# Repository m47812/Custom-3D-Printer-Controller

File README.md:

# Custom-3D-Printer-Controller
A fully custom 3D Printer controller board based on a stm32f7 controller with TMC2209 stepper drivers

## Summary

This Repo contains the design files for a fully custom 3D printer controller board. It is equipped with an STM32F7 Controller and uses custom-made 
TMC2209 Driver PCBs (also included in the Repo). The PCB was designed for using JLCPCBs Assembly service, so most of the SMD parts can directly be assembled by them. 
The Controller PCB is a two layer board, which makes production for hobby projects more affordable.

## Repo Content
The Project contains 3 Folders with KiCad design files.
- Main board: The main board PCB containing the STM32

- Motor Driver: The TMC2209 Motor Driver Plug-In Board

- Handheld: A Handheld device that can be connected via SPI to manually drive the stepper motors.

## Key Points
- STM32F7 Controller
- TMC2209 Stepper Driver
- 24V Power Supply
- USB-B Micro
- Micro SD-Card Slot
- Z Stepper Drivers Allow for simple parallel and serial motor connection
- 3 End stops
- 4 Fan Ports
  - 1 Individually PWM controllable
  - 2 PWM Controllable together
  - 1 Always On
- Support of two Extruders
- SWD Programming Interface
- SPI Connector
- UART Connector
- Buffer Battery
- WLAN Module

## Background
I designed this 3D printer controller as a hobby project, for my own 3D printer. The original plan was to build a custom hardware and custom firmware. Throughout 
the project my colleague and I have moved to a different printer design which resulted in the stop of the firmware project. The PCB was produced at JLCPCB and I did
some tests with it. I've decided to make the project open source for anyone who would like to build their own 3D printer electronics. The project may serve as a starting point or something to enhance, modify and customize.

## State of the project

Since the project was not continued on the firmware side, I did not have the possibility of testing all features to a full degree. My tests manly focused on using the
the motor drivers together with the STM32. I haven't found any problems so far with the PCB, but I would advise looking over it yourself before you order it. 

### Functions I used
- Use of Motor Drivers with STM32 Controller (Configuration via UART & and Control via Step Dir interface)
- Communication via USB
- Power supply from 24V and USB (controller only without motors for USB power)
- Programming with ST-Link

### Untested Functions
- Temperature Measurements
- Temperature control of Bed and Extruders
- SD Card Slot
- WLAN Module
- Buffer Battery

## Firmware
I would recommend using the board with [Marlin firmware](https://github.com/MarlinFirmware/Marlin). It will require some manual adaptations to be able to use Marlin.
Since I haven't used Marlin in my own project, I can not provide these adaptations here.

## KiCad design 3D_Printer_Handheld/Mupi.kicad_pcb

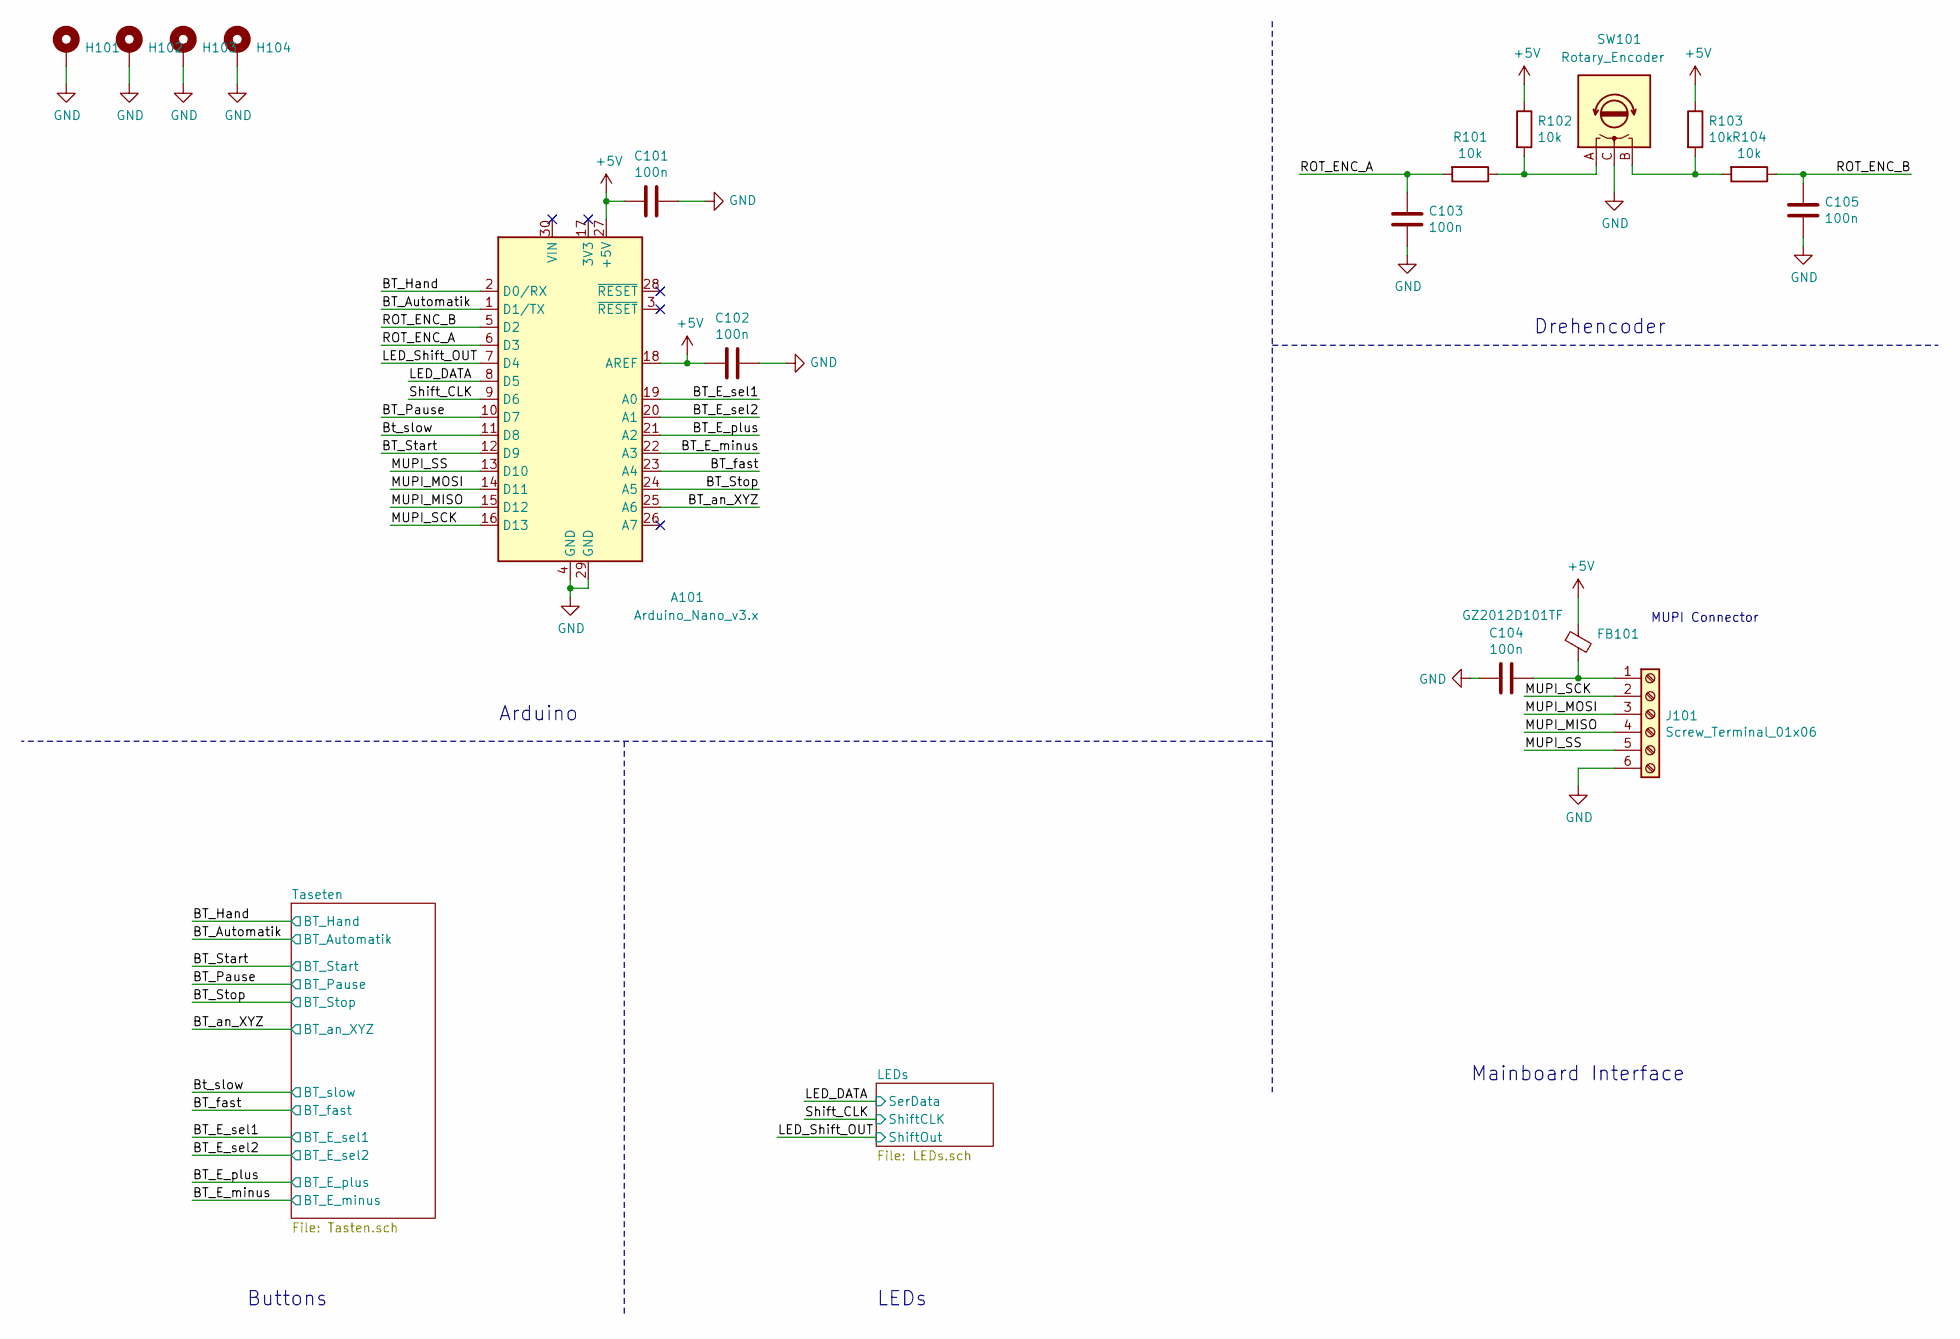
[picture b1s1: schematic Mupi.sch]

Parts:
A101: Arduino_Nano_v3.x; Arduino_Nano
C101, C102, C103, C104, C105: 100n; C_0805_2012Metric_Pad1.15x1.40mm_HandSolder
FB101: GZ2012D101TF; R_0805_2012Metric
H101, H102, H103, H104: MountingHole_Pad; MountingHole_3.2mm_M3_Pad_Via
J101: Screw_Terminal_01x06; TerminalBlock_Phoenix_MPT-0,5-6-2.54_1x06_P2.54mm_Horizontal
R101, R102, R103, R104: 10k; R_0805_2012Metric_Pad1.15x1.40mm_HandSolder
SW101: Rotary_Encoder; RotaryEncoder_Alps_EC12E_Vertical_H20mm

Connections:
+5V: A101.18 (AREF), A101.27 (+5V), C101.2, C102.2, FB101.1, R102.1, R103.1; also elsewhere on the board
/BT_Automatik: A101.1 (D1/TX); also elsewhere on the board
/BT_E_minus: A101.22 (A3); also elsewhere on the board
/BT_E_plus: A101.21 (A2); also elsewhere on the board
/BT_E_sel1: A101.19 (A0); also elsewhere on the board
/BT_E_sel2: A101.20 (A1); also elsewhere on the board
/BT_Hand: A101.2 (D0/RX); also elsewhere on the board
/BT_Pause: A101.10 (D7); also elsewhere on the board
/BT_Start: A101.12 (D9); also elsewhere on the board
/BT_Stop: A101.24 (A5); also elsewhere on the board
/BT_an_XYZ: A101.25 (A6); also elsewhere on the board
/BT_fast: A101.23 (A4); also elsewhere on the board
/Bt_slow: A101.11 (D8); also elsewhere on the board
/LED_DATA: A101.8 (D5); also elsewhere on the board
/LED_Shift_OUT: A101.7 (D4); also elsewhere on the board
/MUPI_MISO: A101.15 (D12), J101.4
/MUPI_MOSI: A101.14 (D11), J101.3
/MUPI_SCK: A101.16 (D13), J101.2
/MUPI_SS: A101.13 (D10), J101.5
/Shift_CLK: A101.9 (D6); also elsewhere on the board
GND: A101.4 (GND), A101.29 (GND), C101.1, C102.1, C103.2, C104.2, C105.2, H101.1, H102.1, H103.1, H104.1, J101.6, SW101.C; also elsewhere on the board
unnamed: C104.1, FB101.2, J101.1
unnamed: R101.1, R102.2, SW101.A
unnamed: R103.2, R104.2, SW101.B

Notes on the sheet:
Drehencoder
MUPI Connector
Mainboard Interface
Buttons
LEDs
Arduino

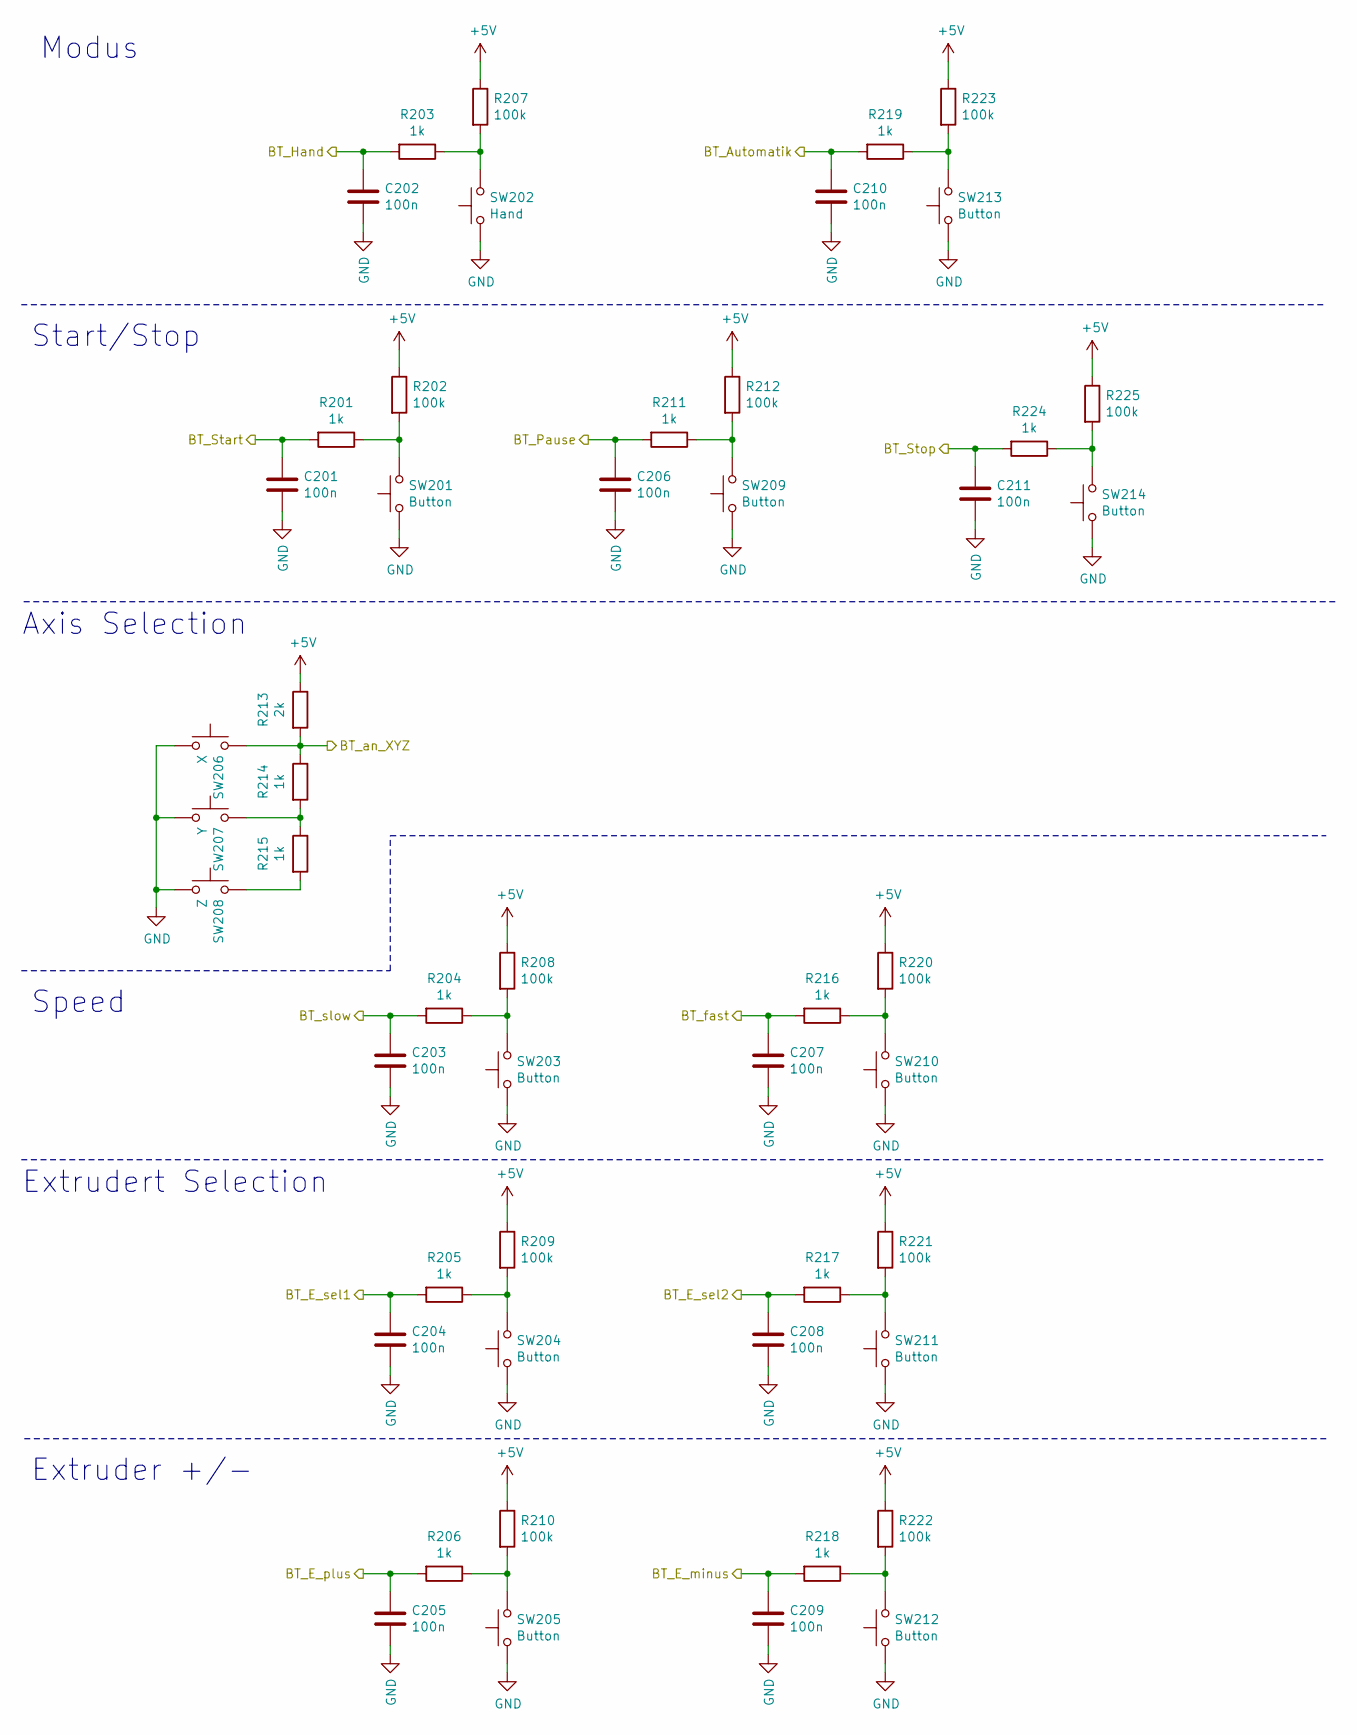
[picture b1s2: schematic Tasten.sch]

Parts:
C201, C202, C203, C204, C205, C206, C207, C208, C209, C210, C211: 100n; C_0805_2012Metric_Pad1.15x1.40mm_HandSolder
R201, R203, R204, R205, R206, R211, R214, R215, R216, R217, R218, R219, R224: 1k; R_0805_2012Metric_Pad1.15x1.40mm_HandSolder
R202, R207, R208, R209, R210, R212, R220, R221, R222, R223, R225: 100k; R_0805_2012Metric_Pad1.15x1.40mm_HandSolder
R213: 2k; R_0805_2012Metric_Pad1.15x1.40mm_HandSolder
SW201, SW203, SW204, SW205, SW209, SW210, SW211, SW212, SW213, SW214: Button; SW_SPST_TL3342
SW202: Hand; SW_SPST_TL3342
SW206: X; SW_SPST_TL3342
SW207: Y; SW_SPST_TL3342
SW208: Z; SW_SPST_TL3342

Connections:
+5V: R202.1, R207.1, R208.1, R209.1, R210.1, R212.1, R213.1, R220.1, R221.1, R222.1, R223.1, R225.1; also elsewhere on the board
/BT_Automatik: C210.2, R219.2; also elsewhere on the board
/BT_E_minus: C209.2, R218.2; also elsewhere on the board
/BT_E_plus: C205.2, R206.2; also elsewhere on the board
/BT_E_sel1: C204.2, R205.2; also elsewhere on the board
/BT_E_sel2: C208.2, R217.2; also elsewhere on the board
/BT_Hand: C202.2, R203.2; also elsewhere on the board
/BT_Pause: C206.2, R211.2; also elsewhere on the board
/BT_Start: C201.2, R201.2; also elsewhere on the board
/BT_Stop: C211.2, R224.2; also elsewhere on the board
/BT_an_XYZ: R213.2, R214.1, SW206.2; also elsewhere on the board
/BT_fast: C207.2, R216.2; also elsewhere on the board
/Bt_slow: C203.2, R204.2; also elsewhere on the board
GND: C201.1, C202.1, C203.1, C204.1, C205.1, C206.1, C207.1, C208.1, C209.1, C210.1, C211.1, SW201.1, SW202.1, SW203.1, SW204.1, SW205.1, SW206.1, SW207.1, SW208.1, SW209.1, SW210.1, SW211.1, SW212.1, SW213.1, SW214.1; also elsewhere on the board
unnamed: R201.1, R202.2, SW201.2
unnamed: R203.1, R207.2, SW202.2
unnamed: R204.1, R208.2, SW203.2
unnamed: R205.1, R209.2, SW204.2
unnamed: R206.1, R210.2, SW205.2
unnamed: R211.1, R212.2, SW209.2
unnamed: R214.2, R215.1, SW207.2
unnamed: R215.2, SW208.2
unnamed: R216.1, R220.2, SW210.2
unnamed: R217.1, R221.2, SW211.2
unnamed: R218.1, R222.2, SW212.2
unnamed: R219.1, R223.2, SW213.2
unnamed: R224.1, R225.2, SW214.2

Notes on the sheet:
Modus
Start/Stop
Axis Selection
Speed
Extrudert Selection
Extruder +/-

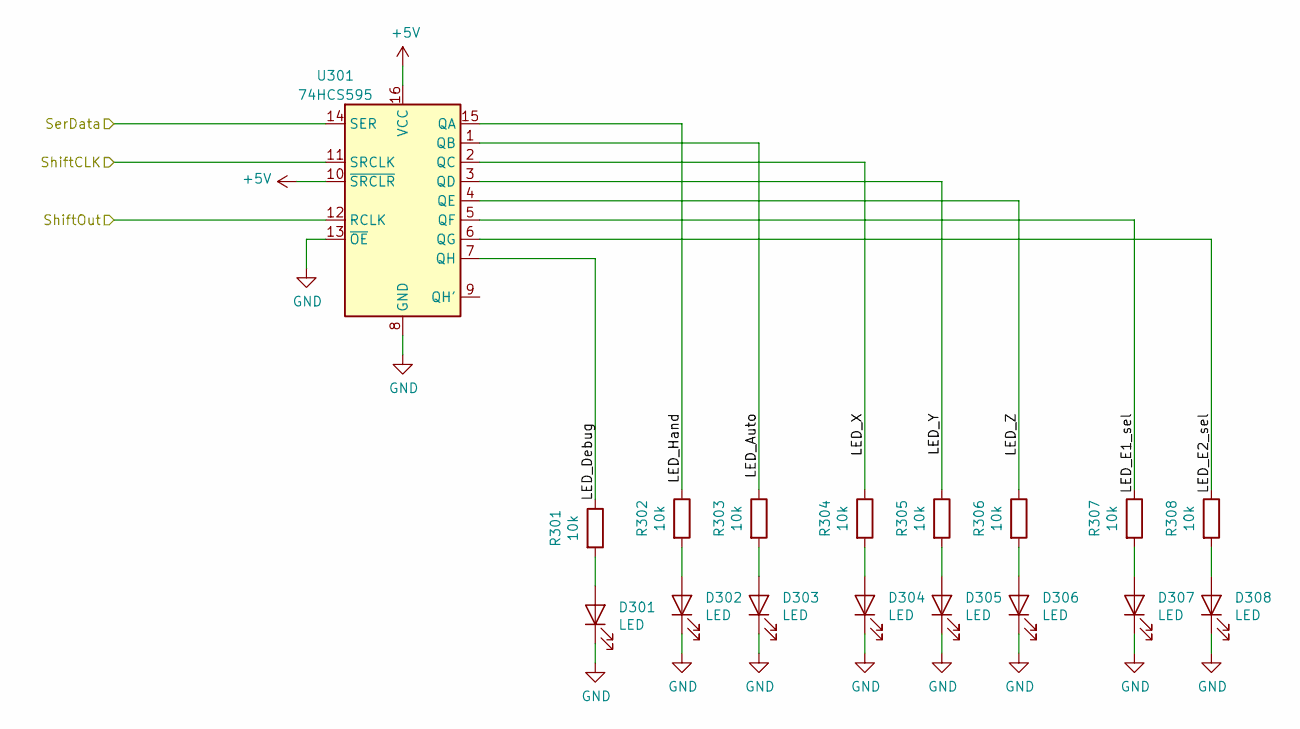
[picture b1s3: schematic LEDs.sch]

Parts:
D301: LED; LED_0603_1608Metric
D302, D303, D304, D305, D306, D307, D308: LED; LED_D3.0mm
R301, R302, R303, R304, R305, R306, R307, R308: 10k; R_0805_2012Metric_Pad1.15x1.40mm_HandSolder
U301: 74HCS595; SOIC-16_3.9x9.9mm_P1.27mm

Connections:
+5V: U301.10 (~SRCLR), U301.16 (VCC); also elsewhere on the board
/LED_DATA: U301.14 (SER); also elsewhere on the board
/LED_Shift_OUT: U301.12 (RCLK); also elsewhere on the board
/LEDs/LED_Auto: R303.1, U301.1 (QB)
/LEDs/LED_Debug: R301.1, U301.7 (QH)
/LEDs/LED_E1_sel: R307.1, U301.5 (QF)
/LEDs/LED_E2_sel: R308.1, U301.6 (QG)
/LEDs/LED_Hand: R302.1, U301.15 (QA)
/LEDs/LED_X: R304.1, U301.2 (QC)
/LEDs/LED_Y: R305.1, U301.3 (QD)
/LEDs/LED_Z: R306.1, U301.4 (QE)
/Shift_CLK: U301.11 (SRCLK); also elsewhere on the board
GND: D301.1 (K), D302.1 (K), D303.1 (K), D304.1 (K), D305.1 (K), D306.1 (K), D307.1 (K), D308.1 (K), U301.8 (GND), U301.13 (~OE); also elsewhere on the board
unnamed: D301.2 (A), R301.2
unnamed: D302.2 (A), R302.2
unnamed: D303.2 (A), R303.2
unnamed: D304.2 (A), R304.2
unnamed: D305.2 (A), R305.2
unnamed: D306.2 (A), R306.2
unnamed: D307.2 (A), R307.2
unnamed: D308.2 (A), R308.2

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
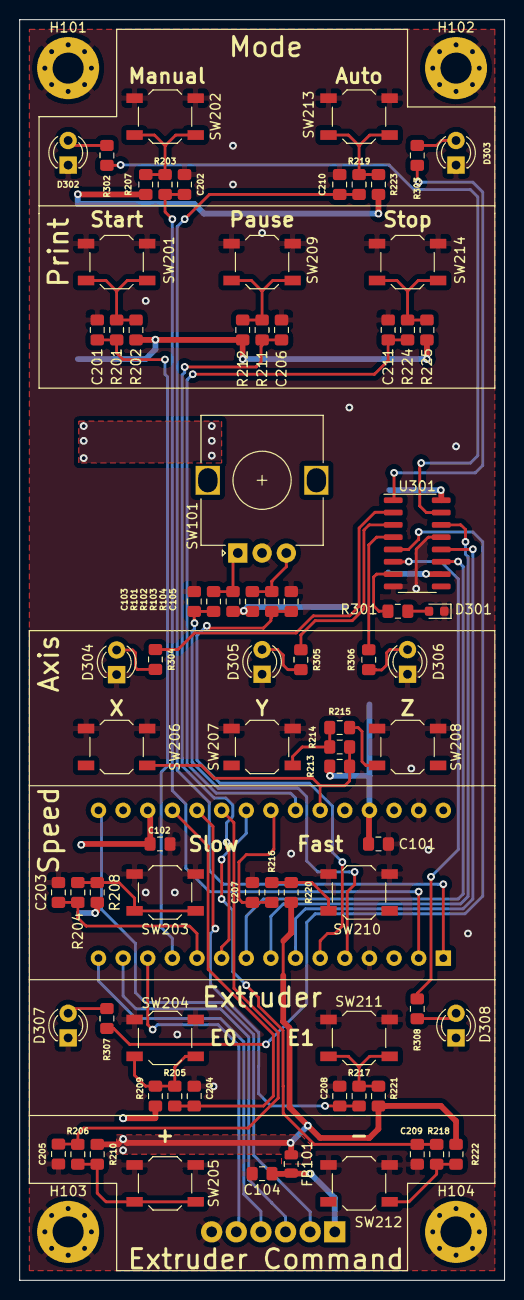
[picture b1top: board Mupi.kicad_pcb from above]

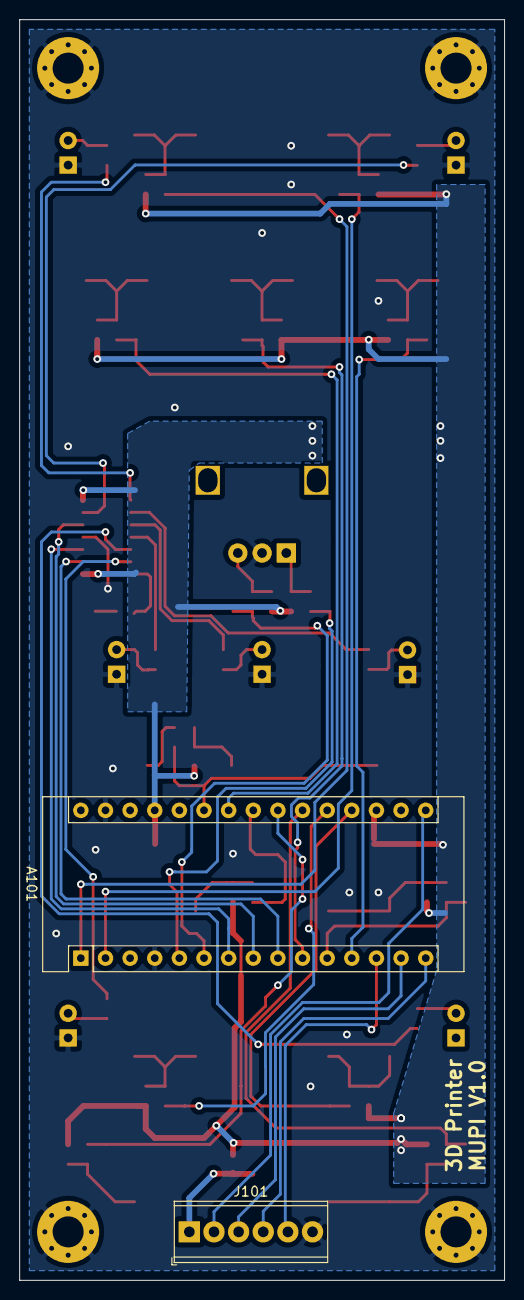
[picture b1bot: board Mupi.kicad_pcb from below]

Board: 2 copper layers, 50.0 x 130.0 mm, 84 parts (2 on the bottom side), 55 nets.

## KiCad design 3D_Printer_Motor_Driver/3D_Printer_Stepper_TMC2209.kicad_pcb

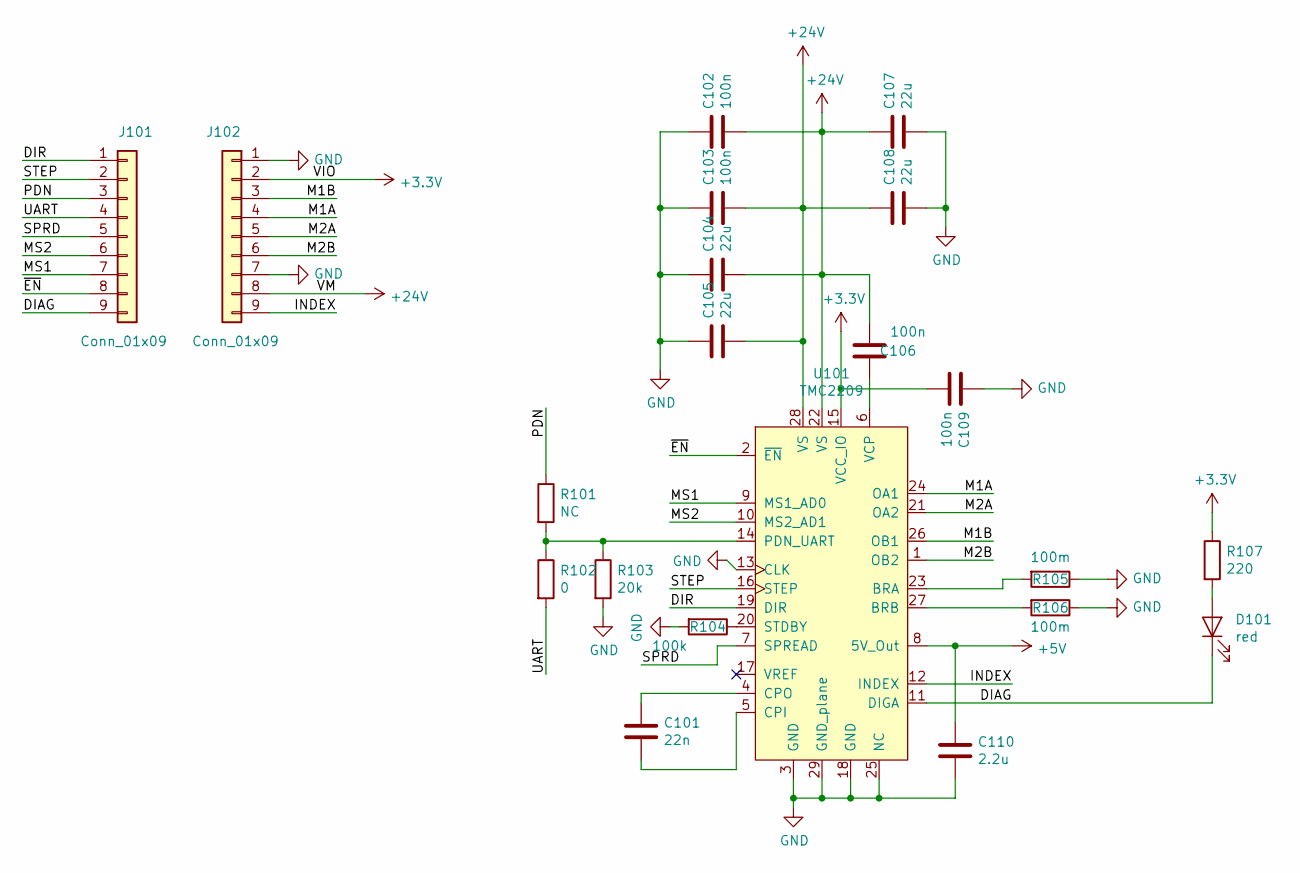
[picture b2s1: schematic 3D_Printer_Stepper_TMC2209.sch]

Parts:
C101: 22n; C_0805_2012Metric
C102, C103, C106, C109: 100n; C_0603_1608Metric
C104, C105, C107, C108: 22u; C_0805_2012Metric
C110: 2.2u; C_0603_1608Metric
D101: red; LED_0603_1608Metric
J101, J102: Conn_01x09; PinHeader_1x09_P2.54mm_Vertical
R101: NC; R_0603_1608Metric_Pad1.05x0.95mm_HandSolder
R102: 0; R_0603_1608Metric_Pad1.05x0.95mm_HandSolder
R103: 20k; R_0402_1005Metric
R104: 100k; R_0402_1005Metric
R105, R106: 100m; R_2512_6332Metric
R107: 220; R_0603_1608Metric
U101: TMC2209; QFN-28-1EP_5x5mm_P0.5mm_EP3.35x3.35mm_ThermalVias

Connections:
+3V3: C109.2, J102.2, R107.1, U101.15 (VCC_IO)
+5V: C110.1, U101.8 (5V_Out)
+24V: C102.2, C103.2, C104.2, C105.2, C106.2, C107.1, C108.1, J102.8, U101.22 (VS), U101.28 (VS)
/DIAG: D101.1 (K), J101.9, U101.11 (DIGA)
/DIR: J101.1, U101.19 (DIR)
/INDEX: J102.9, U101.12 (INDEX)
/M1A: J102.4, U101.24 (OA1)
/M1B: J102.3, U101.26 (OB1)
/M2A: J102.5, U101.21 (OA2)
/M2B: J102.6, U101.1 (OB2)
/MS1: J101.7, U101.9 (MS1_AD0)
/MS2: J101.6, U101.10 (MS2_AD1)
/PDN: J101.3, R101.1
/SPRD: J101.5, U101.7 (SPREAD)
/STEP: J101.2, U101.16 (STEP)
/UART: J101.4, R102.2
/~EN: J101.8, U101.2 (~EN)
GND: C102.1, C103.1, C104.1, C105.1, C107.2, C108.2, C109.1, C110.2, J102.1, J102.7, R103.2, R104.2, R105.1, R106.1, U101.3 (GND), U101.13 (CLK), U101.18 (GND), U101.25 (NC), U101.29 (GND_plane)
unnamed: C101.1, U101.4 (CPO)
unnamed: C101.2, U101.5 (CPI)
unnamed: C106.1, U101.6 (VCP)
unnamed: D101.2 (A), R107.2
unnamed: R101.2, R102.1, R103.1, U101.14 (PDN_UART)
unnamed: R104.1, U101.20 (STDBY)
unnamed: R105.2, U101.23 (BRA)
unnamed: R106.2, U101.27 (BRB)

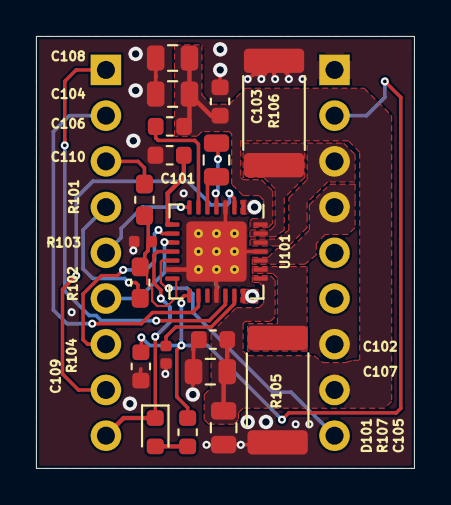
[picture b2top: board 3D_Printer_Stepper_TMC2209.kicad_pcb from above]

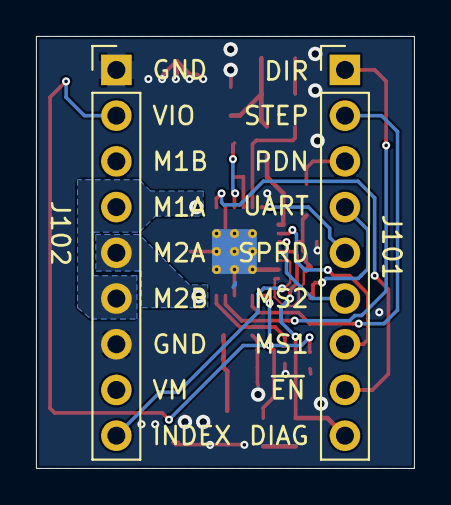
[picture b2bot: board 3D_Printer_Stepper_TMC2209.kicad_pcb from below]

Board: 2 copper layers, 21.0 x 24.0 mm, 21 parts (2 on the bottom side), 26 nets.

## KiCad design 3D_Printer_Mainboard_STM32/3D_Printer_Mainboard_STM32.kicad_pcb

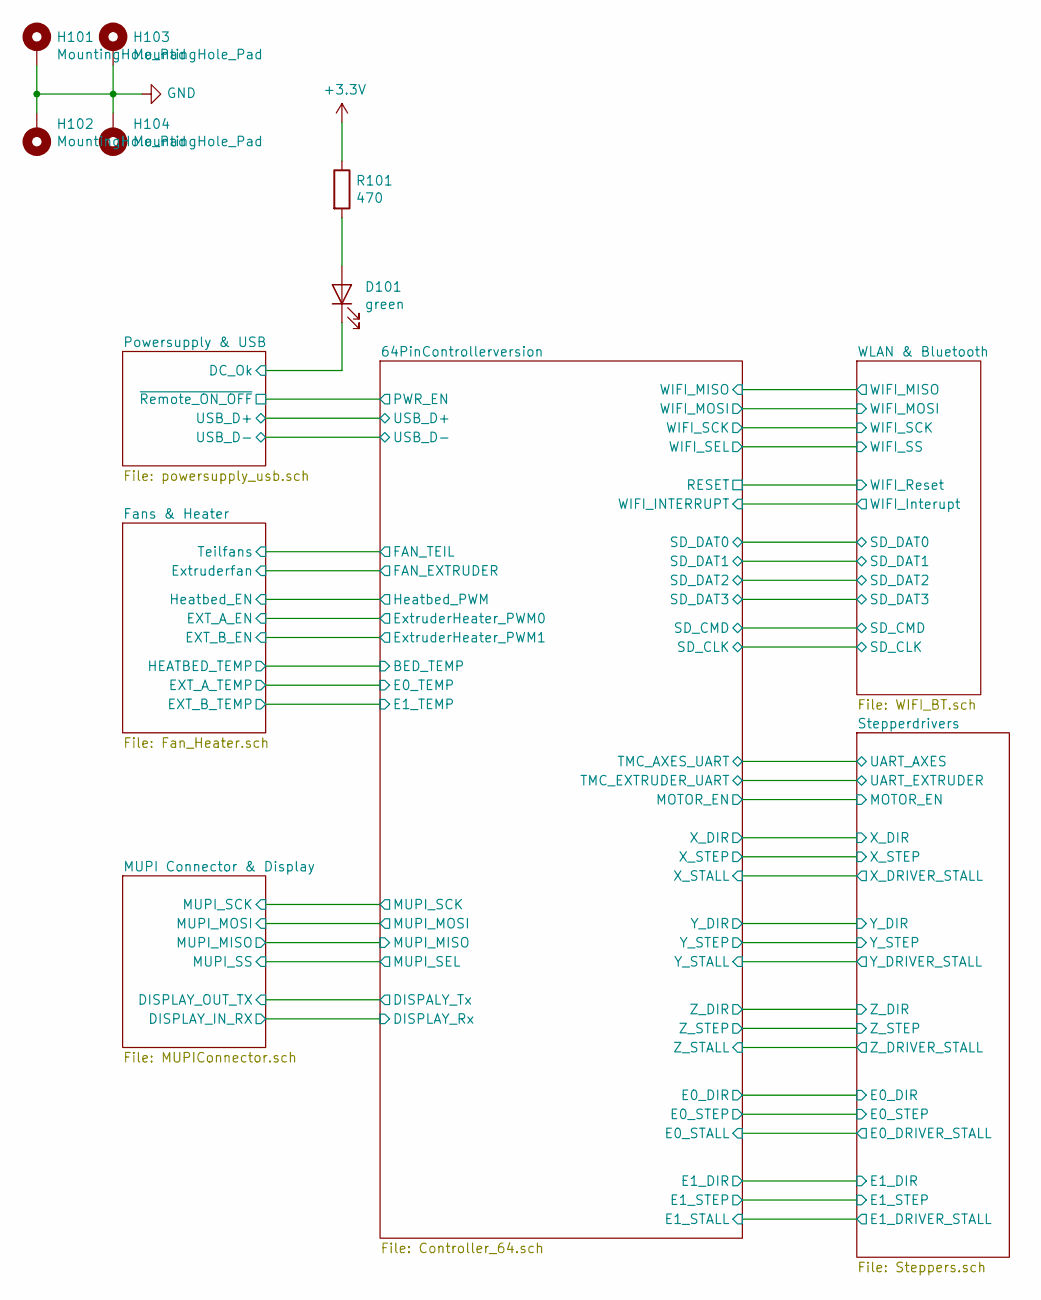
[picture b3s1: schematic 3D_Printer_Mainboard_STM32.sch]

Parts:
D101: green; LED_0603_1608Metric
H101, H102, H103, H104: MountingHole_Pad; MountingHole_4.3mm_M4_Pad_Via
R101: 470; R_0603_1608Metric

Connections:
+3V3: R101.1; also elsewhere on the board
/Powersupply & USB/DC_Ok: D101.1 (K); also elsewhere on the board
GND: H101.1, H102.1, H103.1, H104.1; also elsewhere on the board
unnamed: D101.2 (A), R101.2

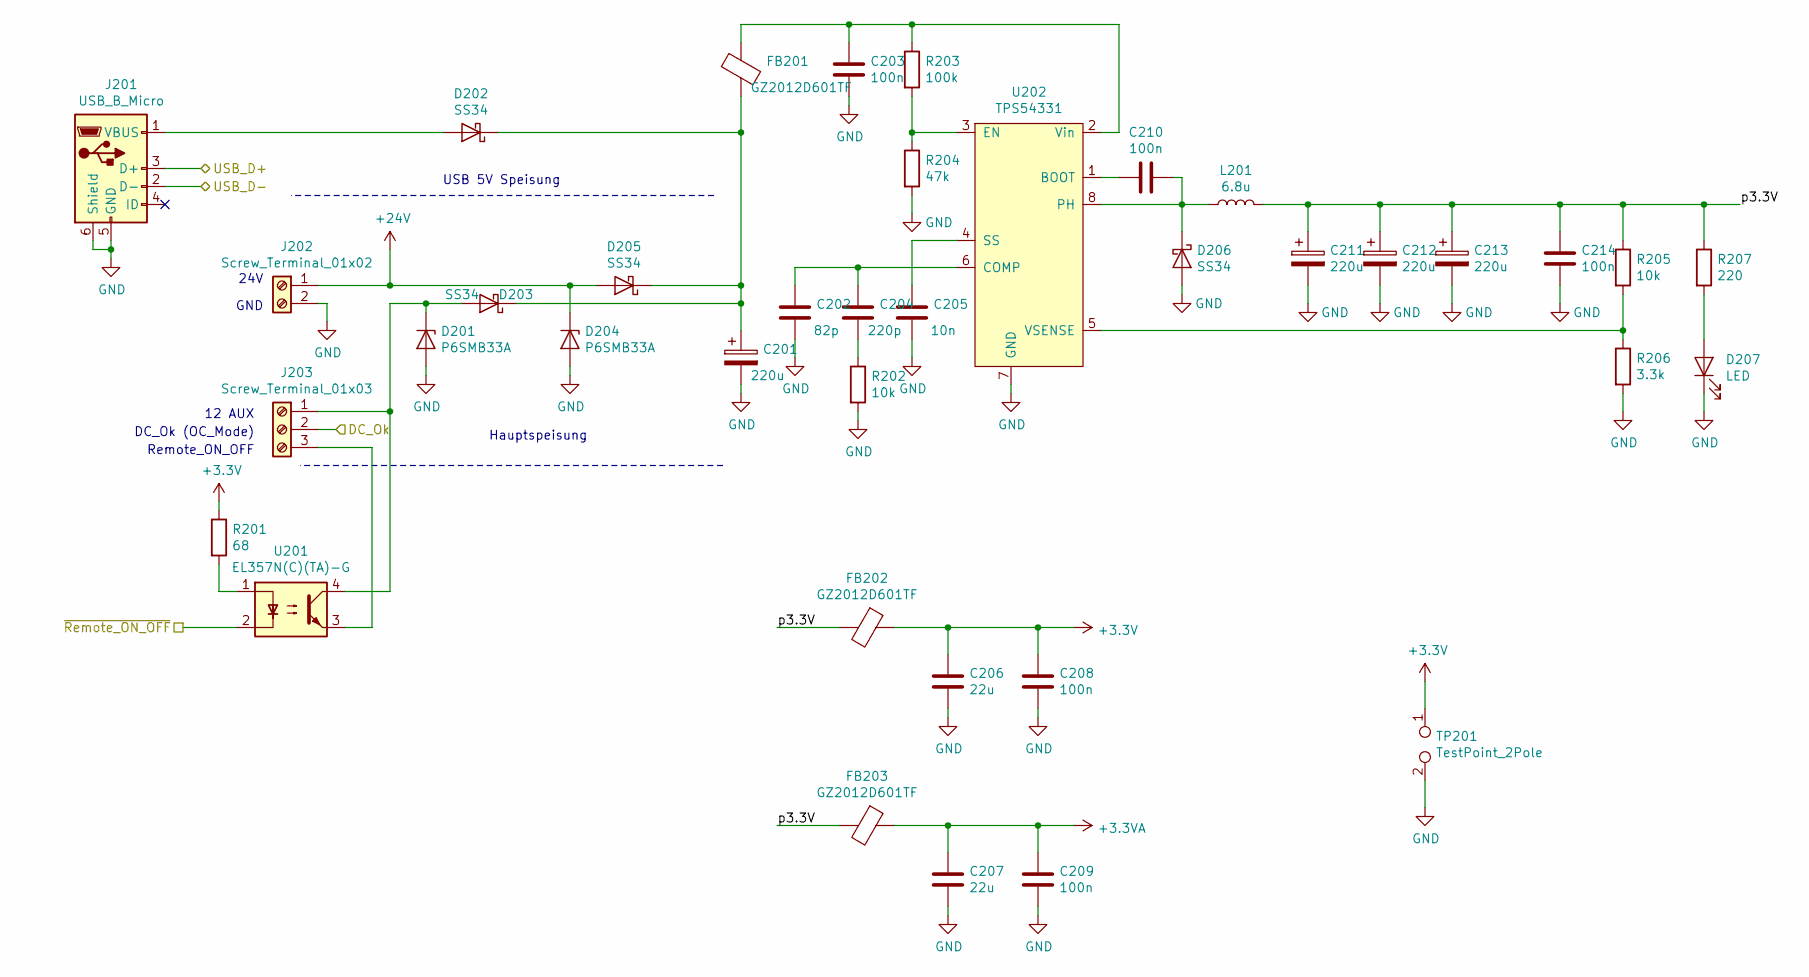
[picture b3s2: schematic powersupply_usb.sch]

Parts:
C201, C211, C212, C213: 220u; CP_Elec_8x10
C202: 82p; C_0603_1608Metric
C203, C210, C214: 100n; C_0603_1608Metric
C204: 220p; C_0603_1608Metric
C205: 10n; C_0603_1608Metric
C206, C207: 22u; C_0603_1608Metric
C208, C209: 100n; C_0402_1005Metric
D201, D204: P6SMB33A; D_SMB
D202, D203, D205, D206: SS34; D_SMA
D207: LED; LED_0603_1608Metric
FB201, FB202, FB203: GZ2012D601TF; C_0805_2012Metric
J201: USB_B_Micro; USB_Micro-B_Wuerth_629105150521_CircularHoles
J202: Screw_Terminal_01x02; 1756993
J203: Screw_Terminal_01x03; TerminalBlock_Phoenix_MPT-0,5-3-2.54_1x03_P2.54mm_Horizontal
L201: 6.8u; L_Sunlord_MWSA0518_5.4x5.2mm
R201: 68; R_0603_1608Metric
R202: 10k; R_0603_1608Metric
R203: 100k; R_0603_1608Metric
R204: 47k; R_0603_1608Metric
R205: 10k; R_0402_1005Metric
R206: 3.3k; R_0402_1005Metric
R207: 220; R_0603_1608Metric
TP201: TestPoint_2Pole; TestPoint_2Pads_Pitch5.08mm_Drill1.3mm
U201: EL357N(C)(TA)-G; SOP-4_3.8x4.1mm_P2.54mm
U202: TPS54331; SOIC-8_3.9x4.9mm_P1.27mm

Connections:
+3.3VA: C207.1, C209.1, FB203.1; also elsewhere on the board
+3V3: C206.1, C208.1, FB202.1, R201.1, TP201.1; also elsewhere on the board
+24V: D204.1 (K), D205.2 (A), J202.1; also elsewhere on the board
/64PinControllerversion/PWR_EN: U201.2; also elsewhere on the board
/64PinControllerversion/USB_D+: J201.3 (D+); also elsewhere on the board
/64PinControllerversion/USB_D-: J201.2 (D-); also elsewhere on the board
/Powersupply & USB/DC_Ok: J203.2; also elsewhere on the board
/Powersupply & USB/p3.3V: C211.1, C212.1, C213.1, C214.1, FB202.2, FB203.2, L201.2, R205.1, R207.1
GND: C201.2, C202.2, C203.2, C205.2, C206.2, C207.2, C208.2, C209.2, C211.2, C212.2, C213.2, C214.2, D201.2 (A), D204.2 (A), D206.2 (A), D207.1 (K), J201.5 (GND), J201.6 (Shield), J202.2, R202.2, R204.2, R206.2, TP201.2, U202.7 (GND); also elsewhere on the board
unnamed: C201.1, D202.1 (K), D203.1 (K), D205.1 (K), FB201.2
unnamed: C202.1, C204.1, U202.6 (COMP)
unnamed: C203.1, FB201.1, R203.1, U202.2 (Vin)
unnamed: C204.2, R202.1
unnamed: C205.1, U202.4 (SS)
unnamed: C210.1, D206.1 (K), L201.1, U202.8 (PH)
unnamed: C210.2, U202.1 (BOOT)
unnamed: D201.1 (K), D203.2 (A), J203.1, U201.4
unnamed: D202.2 (A), J201.1 (VBUS)
unnamed: D207.2 (A), R207.2
unnamed: J203.3, U201.3
unnamed: R201.2, U201.1
unnamed: R203.2, R204.1, U202.3 (EN)
unnamed: R205.2, R206.1, U202.5 (VSENSE)

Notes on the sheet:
USB 5V Speisung
Hauptspeisung
24V
12 AUX
DC_Ok (OC_Mode)
Remote_ON_OFF
GND

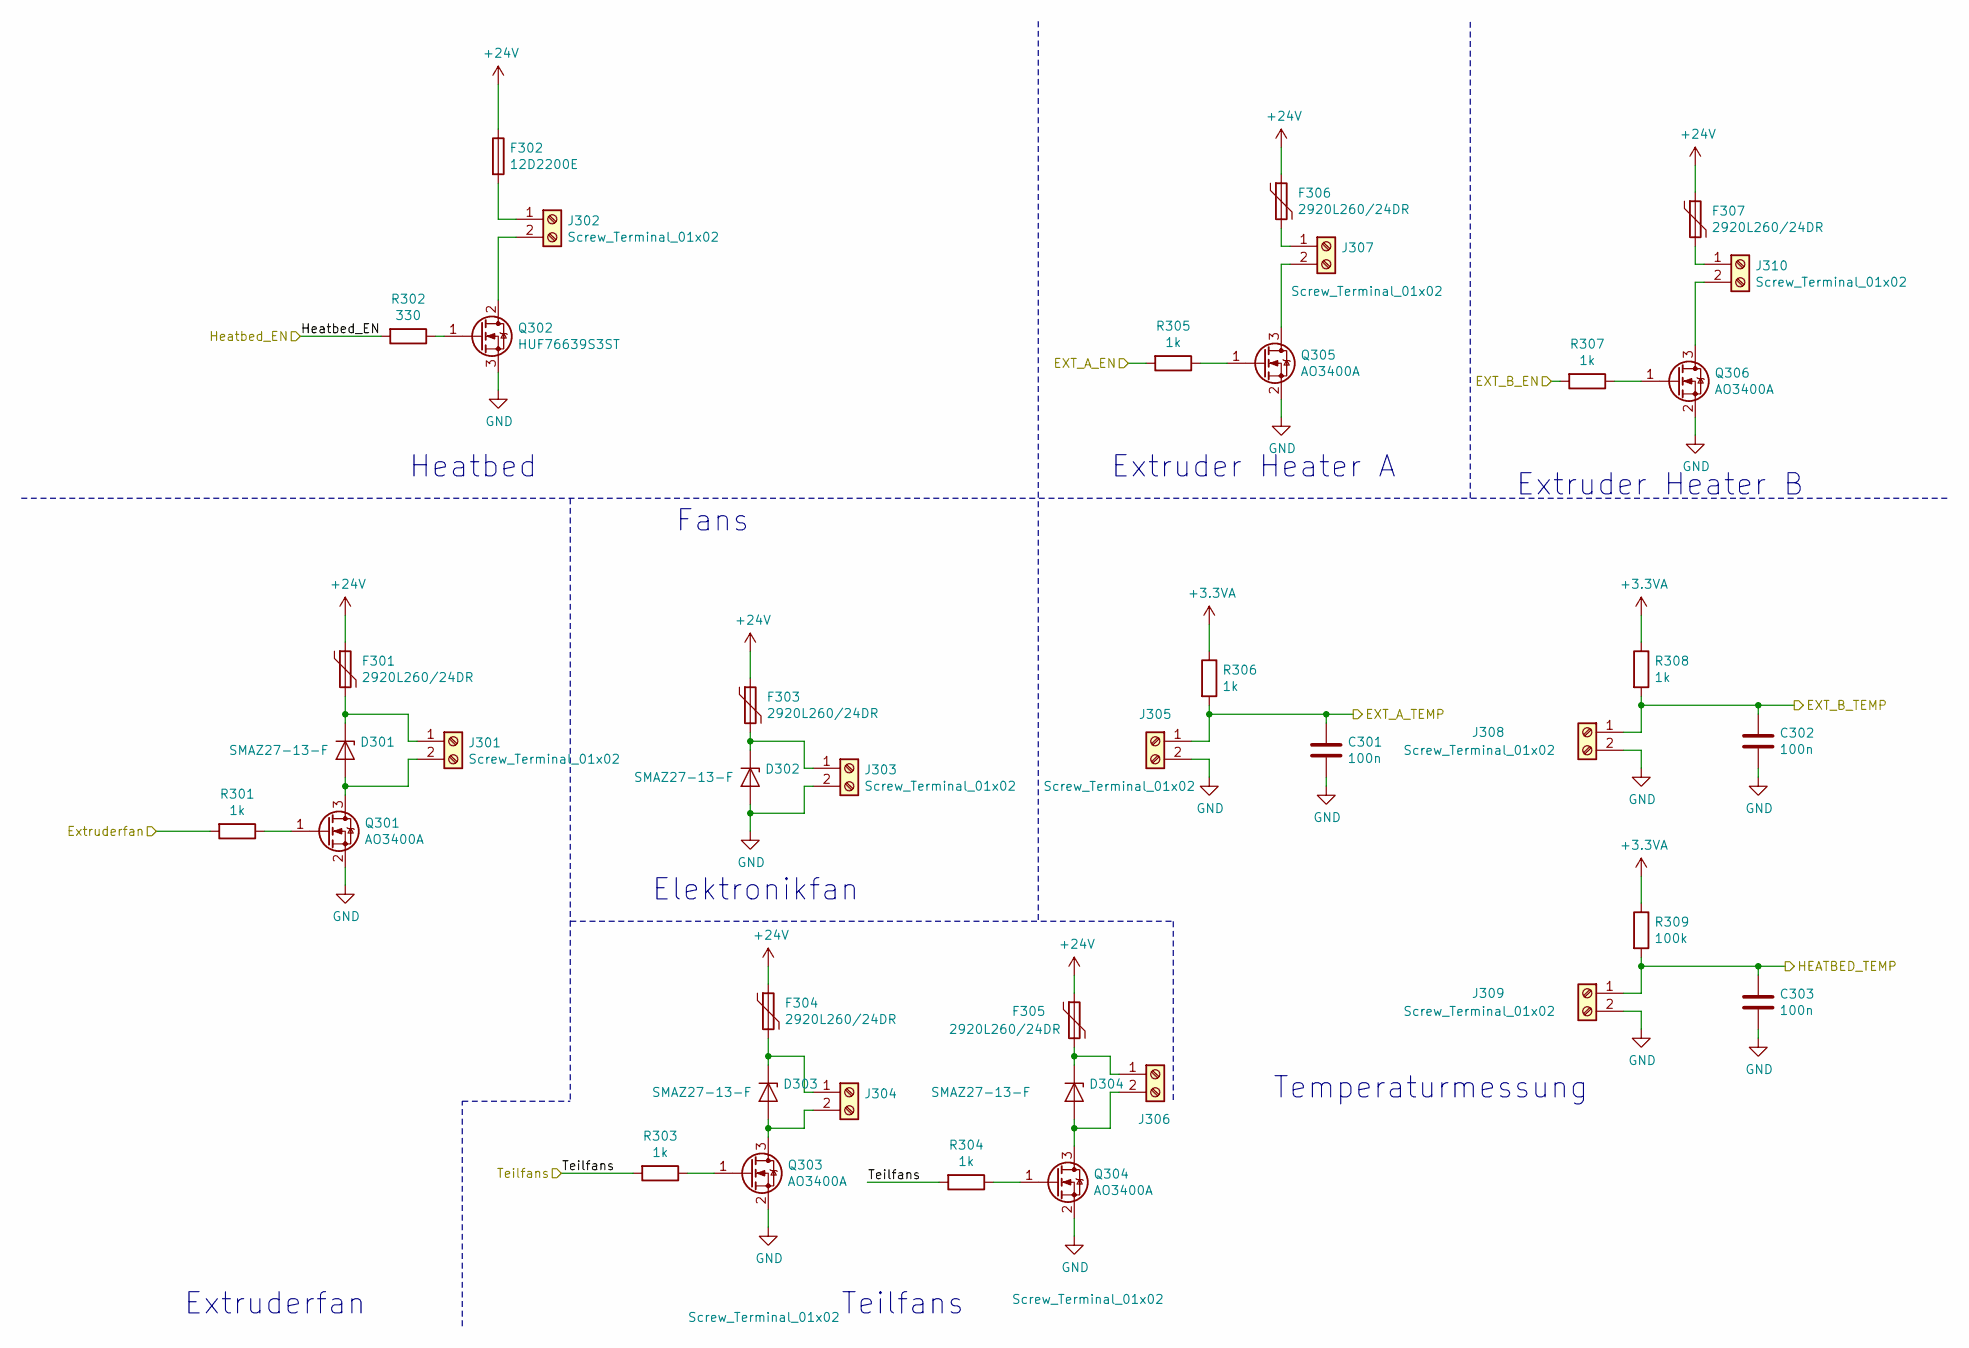
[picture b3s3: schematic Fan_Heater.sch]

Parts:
C301, C302, C303: 100n; C_0402_1005Metric
D301, D302, D303, D304: SMAZ27-13-F; D_SMA
F301, F303, F304, F305, F306, F307: 2920L260/24DR; Fuse_2920_7451Metric
F302: 12D2200E; Fuse_1206_3216Metric
J301, J303, J304, J305, J306, J307, J308, J309, J310: Screw_Terminal_01x02; TerminalBlock_Phoenix_MPT-0,5-2-2.54_1x02_P2.54mm_Horizontal
J302: Screw_Terminal_01x02; TerminalBlock_Phoenix_PT-1,5-2-3.5-H_1x02_P3.50mm_Horizontal
Q301, Q303, Q304, Q305, Q306: AO3400A; SOT-23
Q302: HUF76639S3ST; TO-263-2
R301, R303, R304, R305, R306, R307, R308: 1k; R_0402_1005Metric
R302: 330; R_0402_1005Metric
R309: 100k; R_0402_1005Metric

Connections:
+3.3VA: R306.1, R308.1, R309.1; also elsewhere on the board
+24V: F301.1, F302.1, F303.1, F304.1, F305.1, F306.1, F307.1; also elsewhere on the board
/64PinControllerversion/BED_TEMP: C303.1, J309.1, R309.2; also elsewhere on the board
/64PinControllerversion/E0_TEMP: C301.1, J305.1, R306.2; also elsewhere on the board
/64PinControllerversion/E1_TEMP: C302.1, J308.1, R308.2; also elsewhere on the board
/64PinControllerversion/FAN_TEIL: R303.2, R304.2; also elsewhere on the board
/Fans & Heater/EXT_A_EN: R305.2; also elsewhere on the board
/Fans & Heater/EXT_B_EN: R307.2; also elsewhere on the board
/Fans & Heater/Extruderfan: R301.2; also elsewhere on the board
/Fans & Heater/Heatbed_EN: R302.2; also elsewhere on the board
GND: C301.2, C302.2, C303.2, D302.2 (A), J303.2, J305.2, J308.2, J309.2, Q301.2 (S), Q302.3 (S), Q303.2 (S), Q304.2 (S), Q305.2 (S), Q306.2 (S); also elsewhere on the board
unnamed: D301.1 (K), F301.2, J301.1
unnamed: D301.2 (A), J301.2, Q301.3 (D)
unnamed: D302.1 (K), F303.2, J303.1
unnamed: D303.1 (K), F304.2, J304.1
unnamed: D303.2 (A), J304.2, Q303.3 (D)
unnamed: D304.1 (K), F305.2, J306.1
unnamed: D304.2 (A), J306.2, Q304.3 (D)
unnamed: F302.2, J302.1
unnamed: F306.2, J307.1
unnamed: F307.2, J310.1
unnamed: J302.2, Q302.2 (D)
unnamed: J307.2, Q305.3 (D)
unnamed: J310.2, Q306.3 (D)
unnamed: Q301.1 (G), R301.1
unnamed: Q302.1 (G), R302.1
unnamed: Q303.1 (G), R303.1
unnamed: Q304.1 (G), R304.1
unnamed: Q305.1 (G), R305.1
unnamed: Q306.1 (G), R307.1

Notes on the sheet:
Teilfans
Extruderfan
Elektronikfan
Extruder Heater A
Extruder Heater B
Temperaturmessung
Fans
Heatbed

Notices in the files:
README.md:
License: GPL
